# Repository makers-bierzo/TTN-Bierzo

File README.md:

# The Things Network Bierzo

## Descripción 

El objetivo es adquirir y compartir conocimientos sobre LoRa, LoRaWAN y The Things Network usando microcontroladores y Raspberry Pi.

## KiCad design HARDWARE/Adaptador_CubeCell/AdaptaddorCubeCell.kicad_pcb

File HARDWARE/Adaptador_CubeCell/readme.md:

# Placa Adaptador CubeCell

Adaptador_CubeCell
Ahora ha sido certificado oficialmente como hardware de código abierto por la Open Source Hardware Association. ¡Felicidades! 

[OSHW Certification Mark](https://certification.oshwa.org/es000044.html)

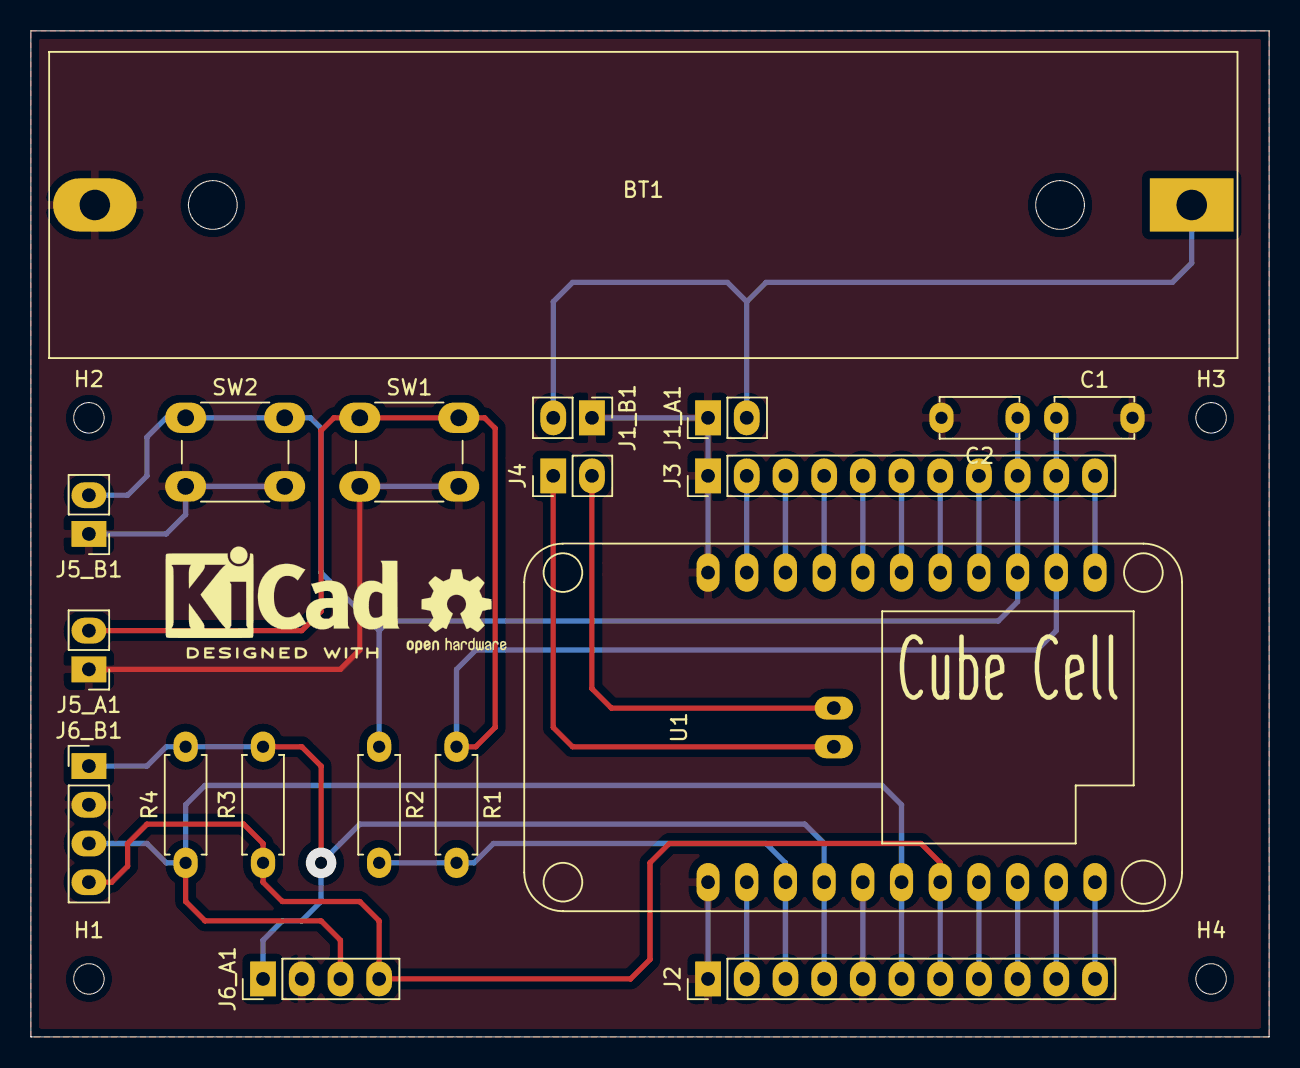
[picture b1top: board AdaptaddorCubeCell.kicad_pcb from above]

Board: 2 copper layers, 81.3 x 66.0 mm, 23 parts (0 on the bottom side), 23 nets.

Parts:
BT1: Battery_Cell; BatteryHolder_MPD_BH-18650-PC2
C1, C2: 1uF; C_Disc_D5.0mm_W2.5mm_P5.00mm
H1, H2, H3, H4: MountingHole_2mm
J1_A1: BAT_1; PinHeader_1x02_P2.54mm_Vertical_custom
J1_B1: BAT_2; PinHeader_1x02_P2.54mm_Vertical_custom
J2: CONECTOR_A; PinHeader_1x11_P2.54mm_Vertical
J3: CONECTOR_B; PinHeader_1x11_P2.54mm_Vertical
J4: CONECTOR_C; PinHeader_1x02_P2.54mm_Vertical_custom
J5_A1: INT1; PinHeader_1x02_P2.54mm_Vertical_custom
J5_B1: INT2; PinHeader_1x02_P2.54mm_Vertical_custom
J6_A1: I2C_A; PinHeader_1x04_P2.54mm_Vertical
J6_B1: I2C_B; PinHeader_1x04_P2.54mm_Vertical
R1, R2, R3, R4: 10K; R_Axial_DIN0207_L6.3mm_D2.5mm_P7.62mm_Horizontal
SW1, SW2: SW_Push; SW_PUSH_6mm_H5mm
U1: CUBECELL_HTCC-AB01; CubeCell_HTCC-AB01

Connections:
+3V3: J2.3, R1.2, R2.2, U1.3
+BATT: BT1.1, J1_A1.2, J1_B1.2
/GPIO1: C1.1, J3.10, J5_A1.2, R1.1, SW1.1, U1.13
/GPIO2: C2.1, J3.9, J5_B1.2, R2.1, SW2.1, U1.14
/SCL: J2.6, J6_A1.3, J6_B1.3, R4.1, U1.6
/SDA: J2.7, J6_A1.4, J6_B1.4, R3.1, U1.7
/VEXT: J2.4, J6_A1.1, J6_B1.1, R3.2, R4.2, U1.4
GND: BT1.2, C1.2, C2.2, J1_A1.1, J1_B1.1, J2.1, J2.5, J3.1, J5_A1.1, J5_B1.1, J6_A1.2, J6_B1.2, SW1.2, SW2.2, U1.1, U1.5, U1.22
unnamed: J2.2, U1.2
unnamed: J2.8, U1.8
unnamed: J2.9, U1.9
unnamed: J2.10, U1.10
unnamed: J2.11, U1.11
unnamed: J3.2, U1.21
unnamed: J3.3, U1.20
unnamed: J3.4, U1.19
unnamed: J3.5, U1.18
unnamed: J3.6, U1.17
unnamed: J3.7, U1.16
unnamed: J3.8, U1.15
unnamed: J3.11, U1.12
unnamed: J4.1, U1.23
unnamed: J4.2, U1.24

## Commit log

2019-04-13 Docu Punto a Punto 01
2019-04-13 Docu Punto a Punto 02
2019-04-14 Docu Punto a Punto 03
2019-04-14 Docu Punto a Punto 04
2019-04-14 Intro lora lorawan y herramientas
2019-04-15 Intro lora-microcontrolador 01
2019-04-16 Lora-microcontrolador 01
2019-04-16 Lora-microcontrolador 02
2019-04-16 Lora-microcontrolador 03
2019-04-16 Lora-microcontrolador v1.0
2019-04-16 Mejoras en la intro
2019-05-01 Cambio de nombres de carpetas
2019-05-01 readme sobre gateways y nodos
2019-05-04 Nano gateway LoPy4
2019-05-18 Nodos LoRa
2019-05-18 Nodos LoRa ABP
2019-05-18 Limpieza de codigo
2019-05-19 Nodos abp v1 y v2
2019-06-06 Nodo con bme280
2019-06-08 Nodo con bme280_01
2019-06-08 Nodo con bme280_02
2019-06-10 Dependencias añadidas al proyecto ttn-abp-ttgov1
2019-07-06 Nodo con Lopy4 con Pysense
2020-01-19 Puesta en marcha con cubecell
2020-02-08 Añadimos lectura de bateria en cubecell
2020-05-29 Añado placa adaptadora para cubecell
2020-05-29 Readme de la placa
2024-02-05 certificación hardware libre
